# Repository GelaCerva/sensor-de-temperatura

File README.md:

# Sensor de Temperatura - Gela Cerva

Sensor de temperatura IoT desenvolvido pela equipe do GelaCerva para possibilitar a medição da temperatura da cerveja de nosso freezer no Garoa Hacker Clube.

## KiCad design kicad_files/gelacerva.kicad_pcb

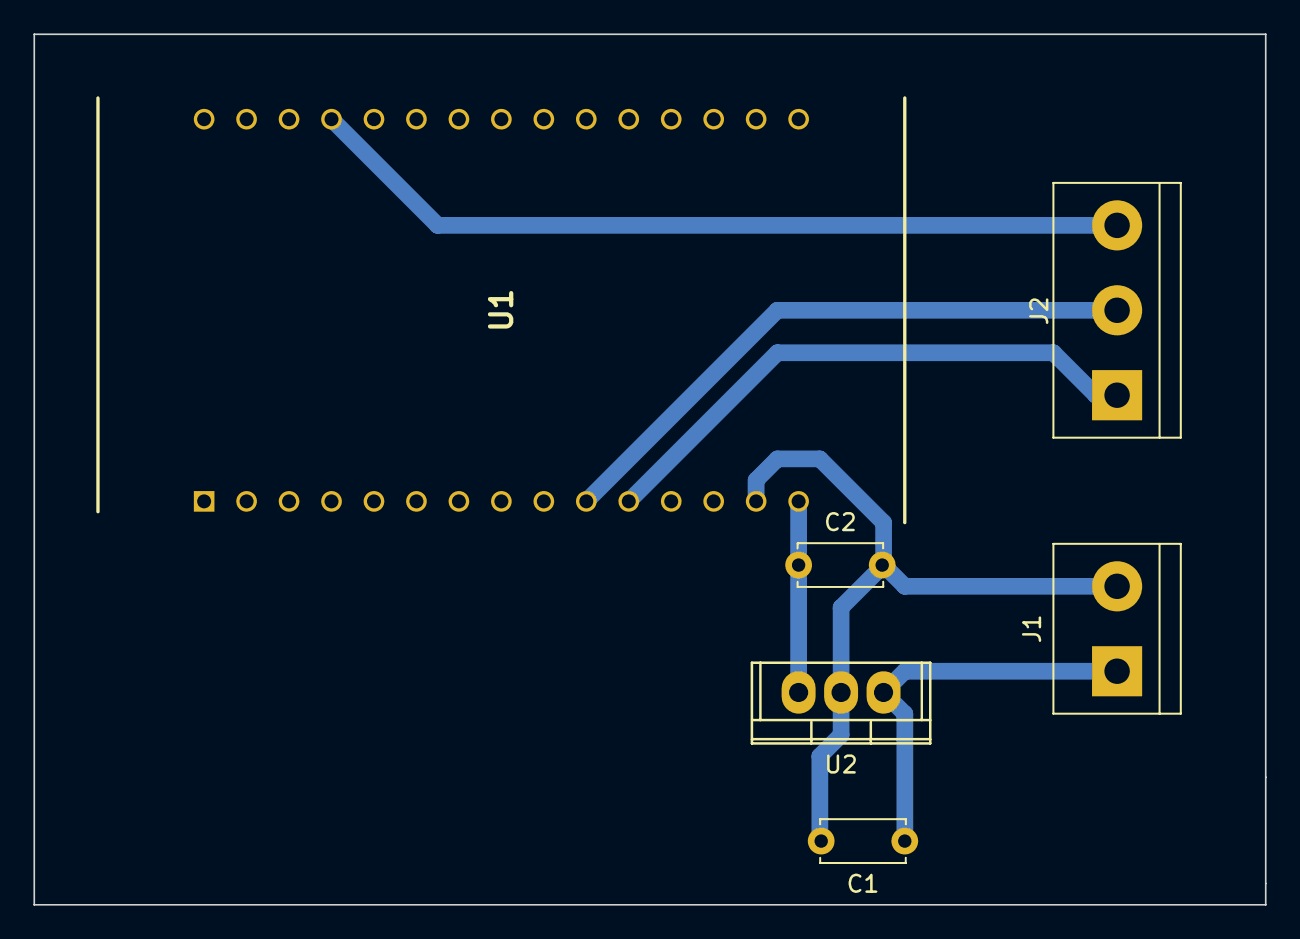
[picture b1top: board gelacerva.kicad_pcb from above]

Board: 2 copper layers, 73.7 x 52.1 mm, 6 parts (0 on the bottom side), 6 nets.

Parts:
C1, C2: C; C_Disc_D5.0mm_W2.5mm_P5.00mm
J1: Screw_Terminal_01x02; TerminalBlock_bornier-2_P5.08mm
J2: Screw_Terminal_01x03; TerminalBlock_bornier-3_P5.08mm
U1: 113990105; DIP2286W64P254L4826H735Q30N
U2: LM7805_TO220; TO-220

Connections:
unnamed: C1.1, J1.1, U2.1
unnamed: C1.2, C2.2, J1.2, U1.14, U2.2
unnamed: C2.1, U1.15, U2.3
unnamed: J2.1, U1.11
unnamed: J2.2, U1.10
unnamed: J2.3, U1.27
